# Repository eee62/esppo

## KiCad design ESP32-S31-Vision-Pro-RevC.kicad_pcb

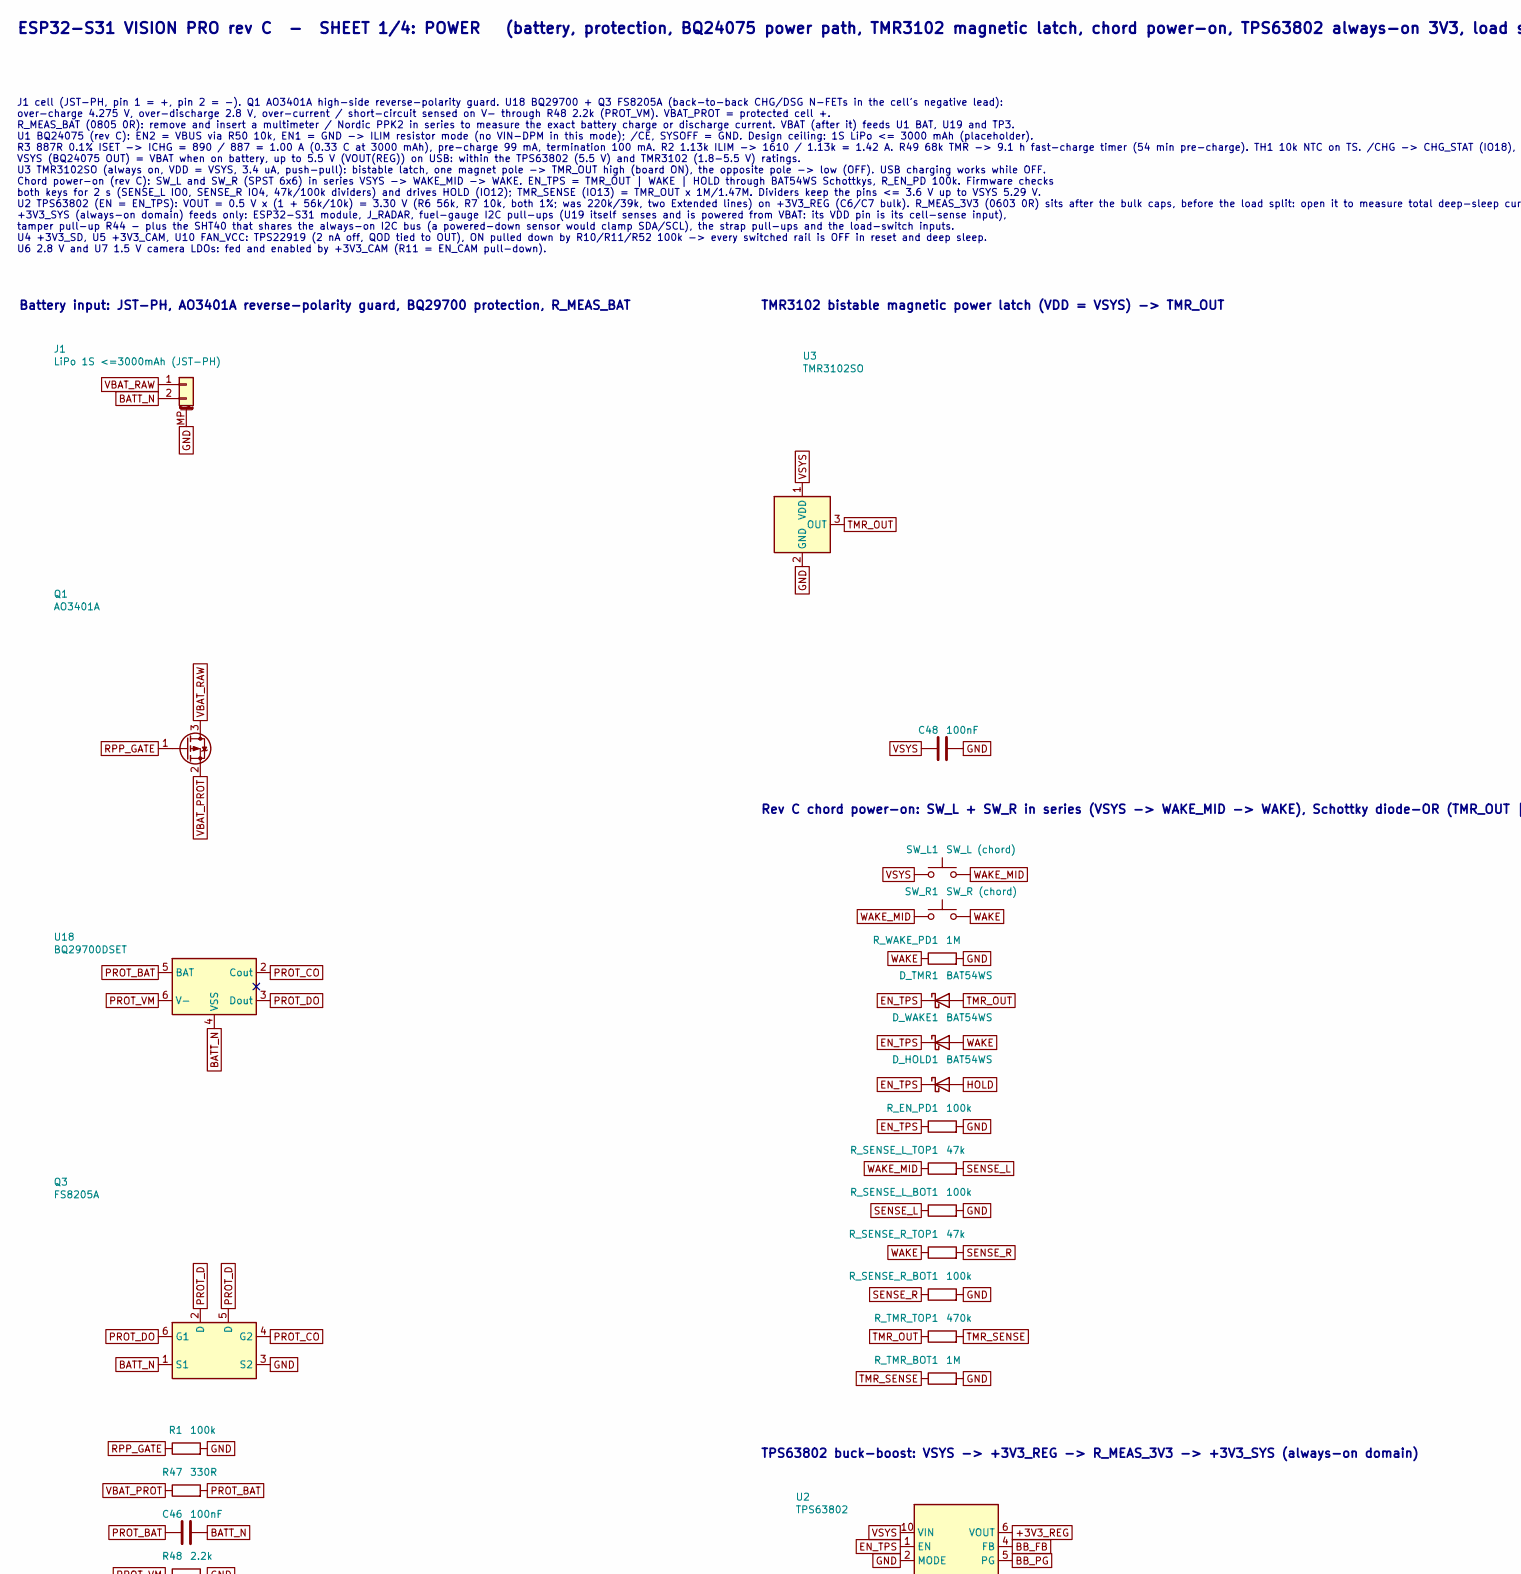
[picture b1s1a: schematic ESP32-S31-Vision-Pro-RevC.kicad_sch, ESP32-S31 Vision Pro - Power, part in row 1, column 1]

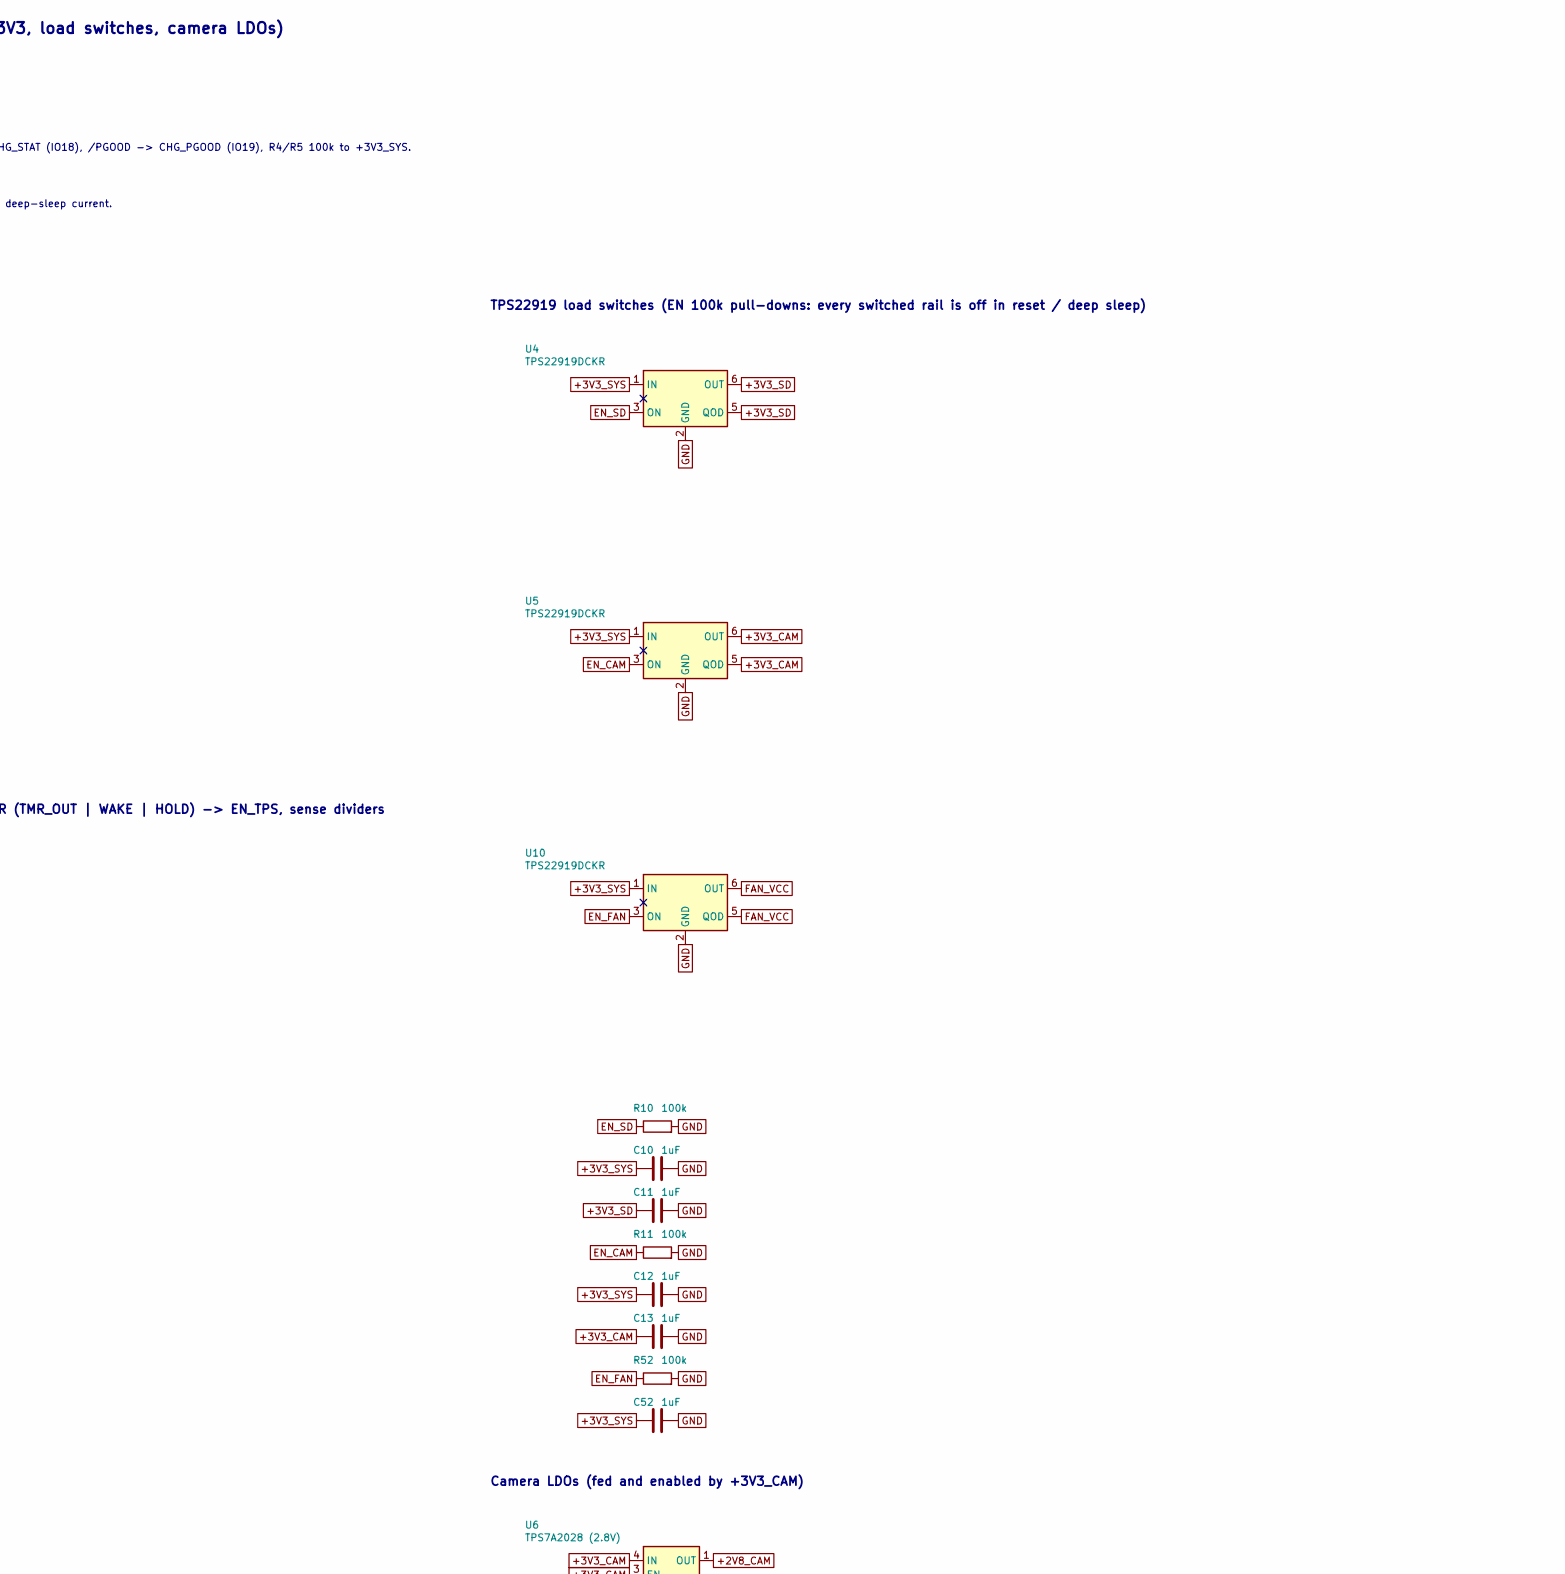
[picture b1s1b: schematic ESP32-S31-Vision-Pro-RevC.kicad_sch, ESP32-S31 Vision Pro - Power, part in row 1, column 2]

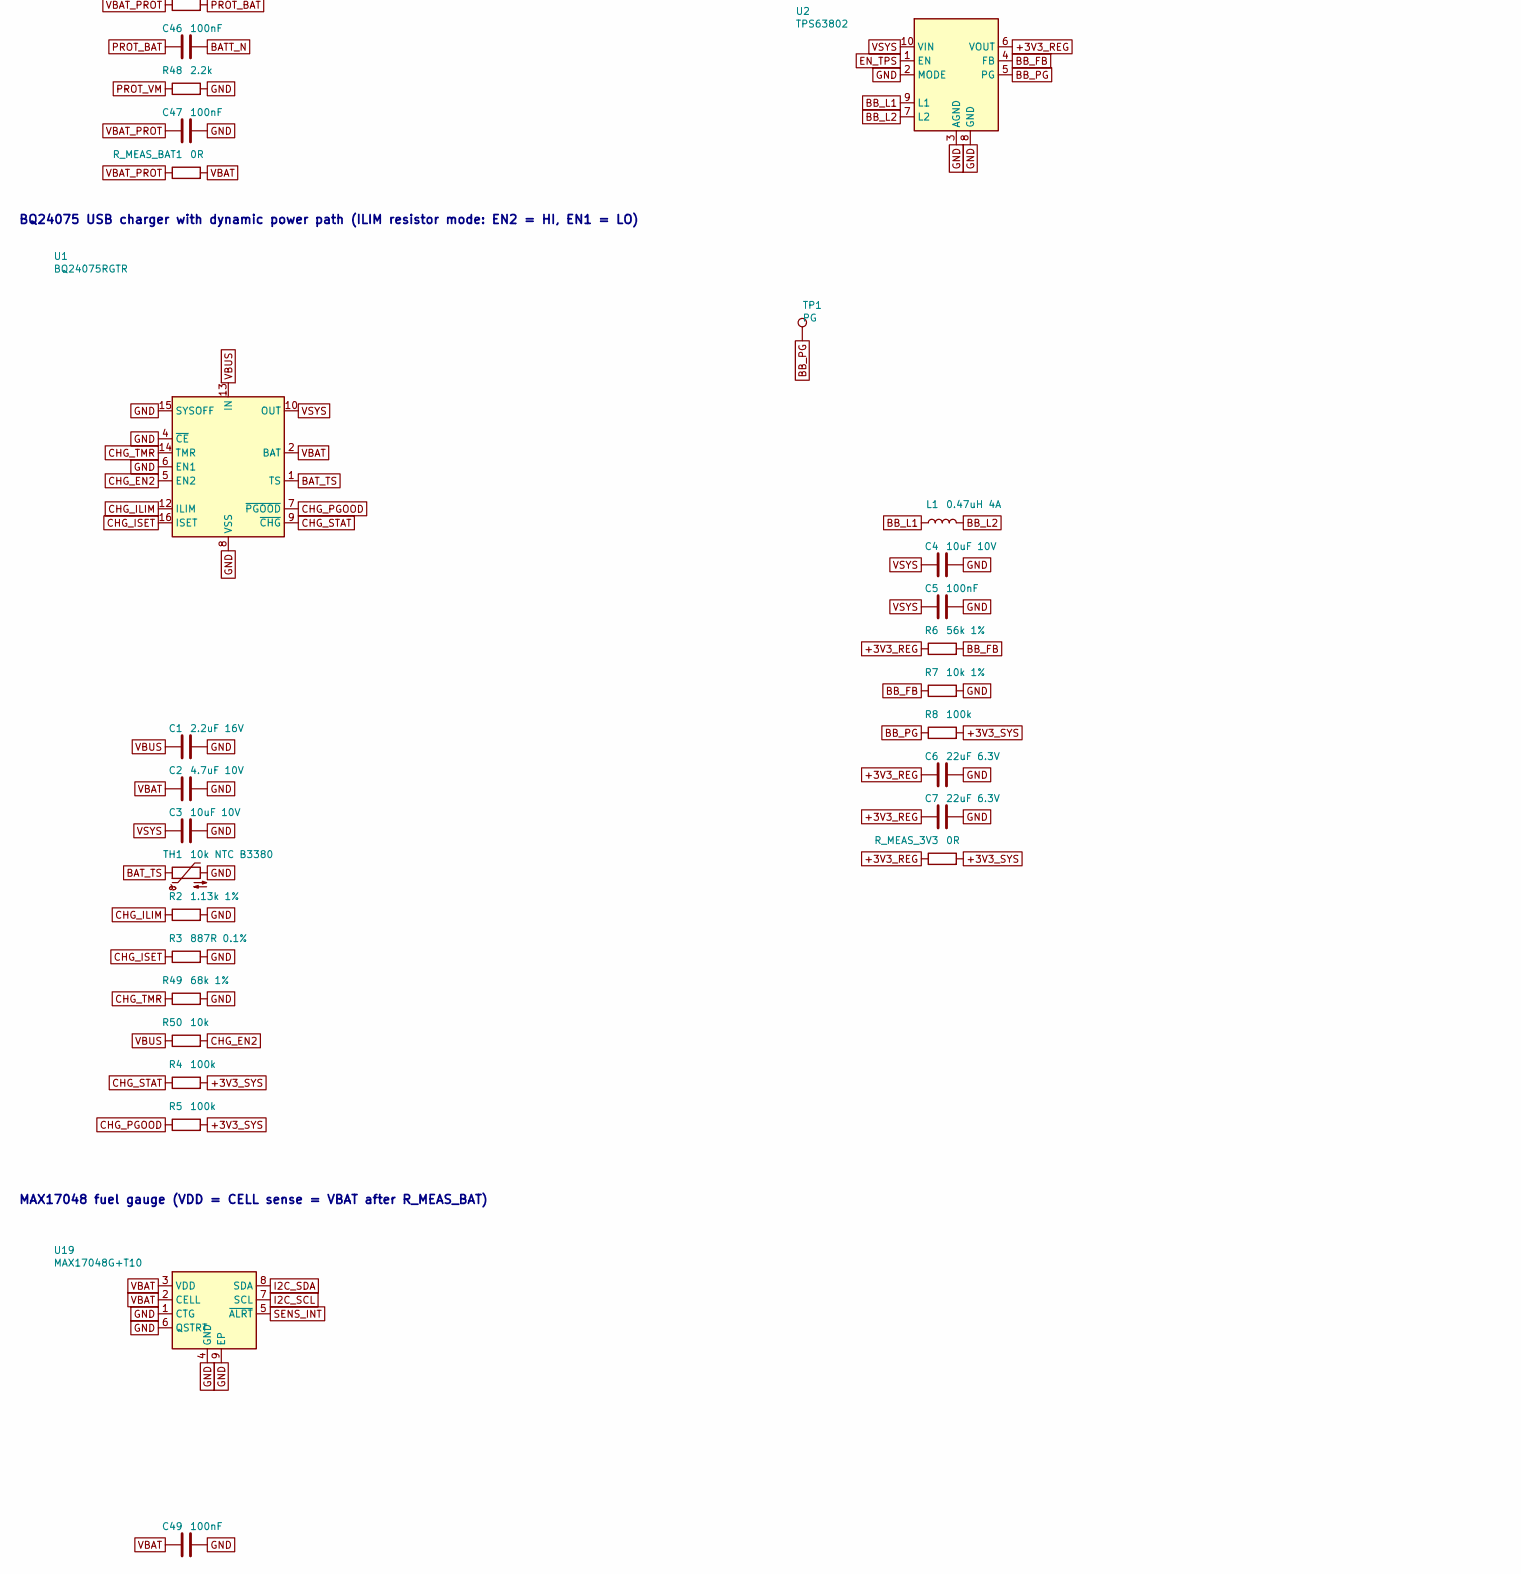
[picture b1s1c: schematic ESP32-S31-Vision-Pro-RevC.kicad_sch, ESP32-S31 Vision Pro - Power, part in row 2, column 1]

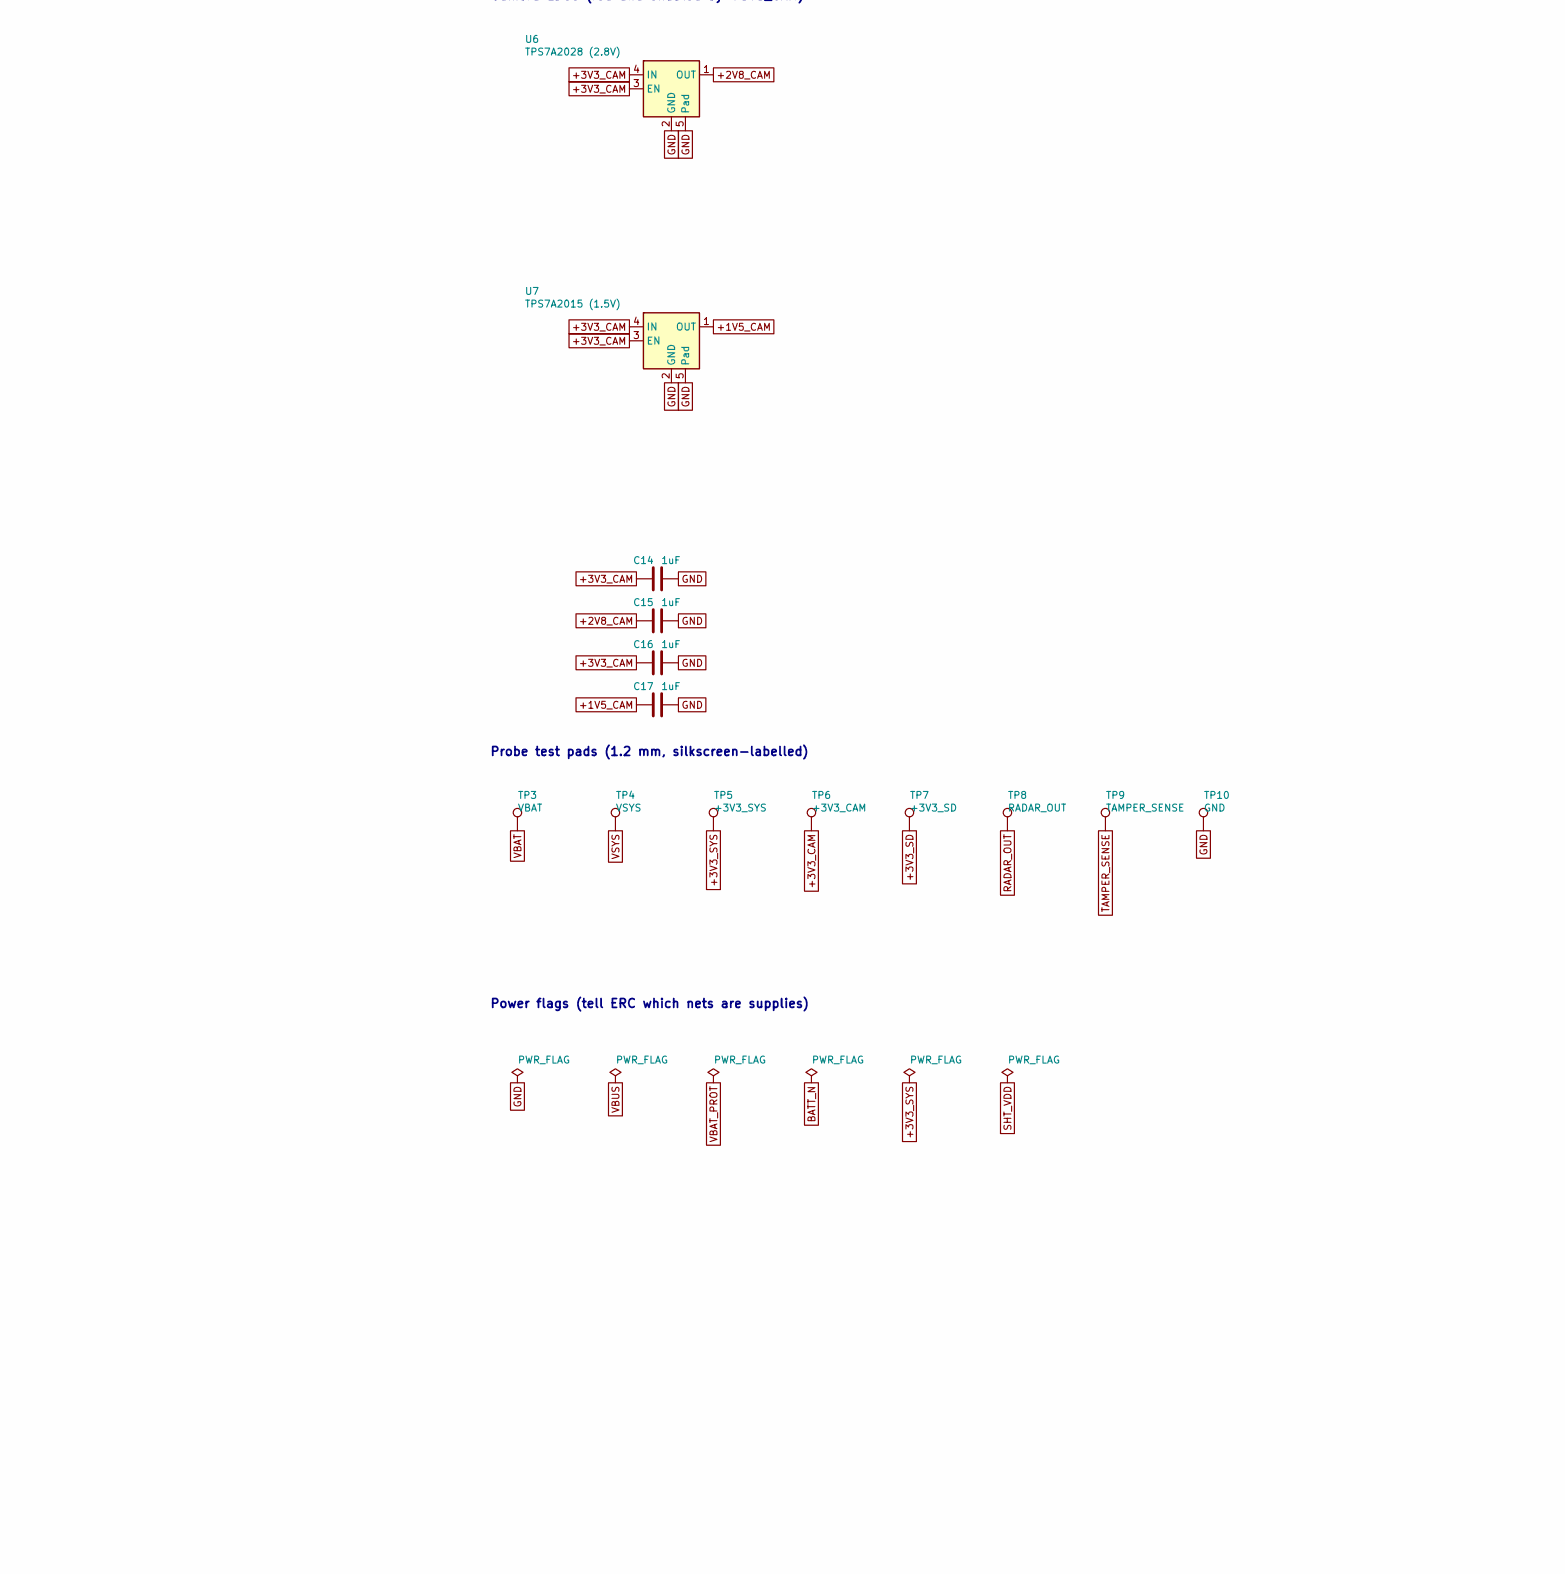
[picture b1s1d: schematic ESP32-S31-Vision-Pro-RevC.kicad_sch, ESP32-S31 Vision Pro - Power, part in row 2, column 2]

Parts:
C1: 2.2uF 16V; C_0603_1608Metric; MPN CL10A225KO8NNNC; LCSC C23630
C2: 4.7uF 10V; C_0603_1608Metric; MPN CL10A475KO8NNNC; LCSC C19666
C3, C4: 10uF 10V; C_0603_1608Metric; MPN CL10A106KP8NNNC; LCSC C19702
C5, C46, C47, C48, C49: 100nF; C_0402_1005Metric; MPN CL05B104KO5NNNC; LCSC C1525
C6, C7: 22uF 6.3V; C_0603_1608Metric; MPN CL10A226MQ8NRNC; LCSC C59461
C10, C11, C12, C13, C14, C15, C16, C17, C52: 1uF; C_0402_1005Metric; MPN CL05A105KA5NQNC; LCSC C52923
D_HOLD1: BAT54WS; D_SOD-323; MPN BAT54WS; LCSC C7502694
D_TMR1: BAT54WS; D_SOD-323; MPN BAT54WS; LCSC C7502694
D_WAKE1: BAT54WS; D_SOD-323; MPN BAT54WS; LCSC C7502694
J1: LiPo 1S <=3000mAh (JST-PH); JST_PH_S2B-PH-SM4-TB_1x02-1MP_P2.00mm_Horizontal; MPN S2B-PH-SM4-TB(LF)(SN); LCSC C295747
L1: 0.47uH 4A; L_1008_2520Metric; MPN DFE252012F-R47M=P2; LCSC C703140
Q1: AO3401A; SOT-23; MPN AO3401A; LCSC C15127
Q3: FS8205A; SOT-23-6; MPN FS8205A; LCSC C908265
R1, R4, R5, R8, R10, R11, R52: 100k; R_0402_1005Metric; MPN 0402WGF1003TCE; LCSC C25741
R2: 1.13k 1%; R_0402_1005Metric; MPN 0402WGF1131TCE; LCSC C67014
R3: 887R 0.1%; R_0402_1005Metric; MPN RT0402BRD07887RL; LCSC C852938
R6: 56k 1%; R_0402_1005Metric; MPN 0402WGF5602TCE; LCSC C25796
R7: 10k 1%; R_0402_1005Metric; MPN 0402WGF1002TCE; LCSC C25744
R47: 330R; R_0402_1005Metric; MPN 0402WGF3300TCE; LCSC C25104
R48: 2.2k; R_0402_1005Metric; MPN 0402WGF2201TCE; LCSC C25879
R49: 68k 1%; R_0402_1005Metric; MPN 0402WGF6802TCE; LCSC C36871
R50: 10k; R_0402_1005Metric; MPN 0402WGF1002TCE; LCSC C25744
R_EN_PD1: 100k; R_0402_1005Metric; MPN 0402WGF1003TCE; LCSC C25741
R_MEAS_3V3: 0R; R_0603_1608Metric; MPN 0603WAF0000T5E; LCSC C21189
R_MEAS_BAT1: 0R; R_0805_2012Metric; MPN 0805W8F0000T5E; LCSC C17477
R_SENSE_L_BOT1: 100k; R_0402_1005Metric; MPN 0402WGF1003TCE; LCSC C25741
R_SENSE_L_TOP1: 47k; R_0402_1005Metric; MPN 0402WGF4702TCE; LCSC C25792
R_SENSE_R_BOT1: 100k; R_0402_1005Metric; MPN 0402WGF1003TCE; LCSC C25741
R_SENSE_R_TOP1: 47k; R_0402_1005Metric; MPN 0402WGF4702TCE; LCSC C25792
R_TMR_BOT1: 1M; R_0402_1005Metric; MPN 0402WGF1004TCE; LCSC C26083
R_TMR_TOP1: 470k; R_0402_1005Metric; MPN 0402WGF4703TCE; LCSC C25790
R_WAKE_PD1: 1M; R_0402_1005Metric; MPN 0402WGF1004TCE; LCSC C26083
SW_L1: SW_L (chord); SW_SPST_PTS645Sx43SMTR92; MPN PTS645SK43SMTR92LFS; LCSC C221871
SW_R1: SW_R (chord); SW_SPST_PTS645Sx43SMTR92; MPN PTS645SK43SMTR92LFS; LCSC C221871
TH1: 10k NTC B3380; R_0402_1005Metric; MPN NCP15XH103F03RC; LCSC C77131
TP1: PG; TestPoint_Pad_D1.0mm
TP3: VBAT; TestPoint_Pad_D1.2mm
TP4: VSYS; TestPoint_Pad_D1.2mm
TP5: +3V3_SYS; TestPoint_Pad_D1.2mm
TP6: +3V3_CAM; TestPoint_Pad_D1.2mm
TP7: +3V3_SD; TestPoint_Pad_D1.2mm
TP8: RADAR_OUT; TestPoint_Pad_D1.2mm
TP9: TAMPER_SENSE; TestPoint_Pad_D1.2mm
TP10: GND; TestPoint_Pad_D1.2mm
U1: BQ24075RGTR; VQFN-16-1EP_3x3mm_P0.5mm_EP1.6x1.6mm; MPN BQ24075RGTR; LCSC C15464
U2: TPS63802; Texas_DLA0010A_VSON-HR-10_2x3mm_P0.5mm; MPN TPS63802DLAT; LCSC C1849531
U3: TMR3102SO; SOT-23; MPN TMR3102SO; LCSC C7421000
U4, U5, U10: TPS22919DCKR; SOT-363_SC-70-6; MPN TPS22919DCKR; LCSC C2149796
U6: TPS7A2028 (2.8V); Texas_X2SON-4_1x1mm_P0.65mm; MPN TPS7A2028PDQNR-A-TP; LCSC C55191366
U7: TPS7A2015 (1.5V); Texas_X2SON-4_1x1mm_P0.65mm; MPN TPS7A2015PDQNR; LCSC C2862700
U18: BQ29700DSET; WSON-6_1.5x1.5mm_P0.5mm; MPN BQ29700DSET; LCSC C2876282
U19: MAX17048G+T10; TDFN-8-1EP_2x2mm_P0.5mm_EP0.8x1.2mm; MPN MAX17048G+T10; LCSC C2682616

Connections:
+1V5_CAM: C17.1, U7.1 (OUT); also elsewhere on the board
+2V8_CAM: C15.1, U6.1 (OUT); also elsewhere on the board
+3V3_CAM: C13.1, C14.1, C16.1, TP6.1, U5.5 (QOD), U5.6 (OUT), U6.3 (EN), U6.4 (IN), U7.3 (EN), U7.4 (IN)
+3V3_REG: C6.1, C7.1, R6.1, R_MEAS_3V3.1, U2.6 (VOUT)
+3V3_SD: C11.1, TP7.1, U4.5 (QOD), U4.6 (OUT); also elsewhere on the board
+3V3_SYS: C10.1, C12.1, C52.1, R4.2, R5.2, R8.2, R_MEAS_3V3.2, TP5.1, U4.1 (IN), U5.1 (IN), U10.1 (IN); also elsewhere on the board
BATT_N: C46.2, J1.2, Q3.1 (S1), U18.4 (VSS)
BAT_TS: TH1.1, U1.1 (TS)
BB_FB: R6.2, R7.1, U2.4 (FB)
BB_L1: L1.1, U2.9 (L1)
BB_L2: L1.2, U2.7 (L2)
BB_PG: R8.1, TP1.1, U2.5 (PG)
CHG_EN2: R50.2, U1.5 (EN2)
CHG_ILIM: R2.1, U1.12 (ILIM)
CHG_ISET: R3.1, U1.16 (ISET)
CHG_PGOOD: R5.1, U1.7 (~PGOOD); also elsewhere on the board
CHG_STAT: R4.1, U1.9 (~CHG); also elsewhere on the board
CHG_TMR: R49.1, U1.14 (TMR)
EN_CAM: R11.1, U5.3 (ON); also elsewhere on the board
EN_FAN: R52.1, U10.3 (ON); also elsewhere on the board
EN_SD: R10.1, U4.3 (ON); also elsewhere on the board
EN_TPS: D_HOLD1.1 (K), D_TMR1.1 (K), D_WAKE1.1 (K), R_EN_PD1.1, U2.1 (EN)
FAN_VCC: U10.5 (QOD), U10.6 (OUT); also elsewhere on the board
GND: C1.2, C2.2, C3.2, C4.2, C5.2, C6.2, C7.2, C10.2, C11.2, C12.2, C13.2, C14.2, C15.2, C16.2, C17.2, C47.2, C48.2, C49.2, C52.2, J1.MP (MountPin), Q3.3 (S2), R1.2, R2.2, R3.2, R7.2, R10.2, R11.2, R48.2, R49.2, R52.2, R_EN_PD1.2, R_SENSE_L_BOT1.2, R_SENSE_R_BOT1.2, R_TMR_BOT1.2, R_WAKE_PD1.2, TH1.2, TP10.1, U1.4 (~CE), U1.6 (EN1), U1.8 (VSS), U1.15 (SYSOFF), U1.17 (VSS), U2.2 (MODE), U2.3 (AGND), U2.8 (GND), U3.2 (GND), U4.2 (GND), U5.2 (GND), U6.2 (GND), U6.5 (Pad), U7.2 (GND), U7.5 (Pad), U10.2 (GND), U19.1 (CTG), U19.4 (GND), U19.6 (QSTRT), U19.9 (EP); also elsewhere on the board
HOLD: D_HOLD1.2 (A); also elsewhere on the board
I2C_SCL: U19.7 (SCL); also elsewhere on the board
I2C_SDA: U19.8 (SDA); also elsewhere on the board
PROT_BAT: C46.1, R47.2, U18.5 (BAT)
PROT_CO: Q3.4 (G2), U18.2 (Cout)
PROT_D: Q3.2 (D), Q3.5 (D)
PROT_DO: Q3.6 (G1), U18.3 (Dout)
PROT_VM: R48.1, U18.6 (V-)
RADAR_OUT: TP8.1; also elsewhere on the board
RPP_GATE: Q1.1 (G), R1.1
SENSE_L: R_SENSE_L_BOT1.1, R_SENSE_L_TOP1.2; also elsewhere on the board
SENSE_R: R_SENSE_R_BOT1.1, R_SENSE_R_TOP1.2; also elsewhere on the board
SENS_INT: U19.5 (~ALRT); also elsewhere on the board
TAMPER_SENSE: TP9.1; also elsewhere on the board
TMR_OUT: D_TMR1.2 (A), R_TMR_TOP1.1, U3.3 (OUT)
TMR_SENSE: R_TMR_BOT1.1, R_TMR_TOP1.2; also elsewhere on the board
VBAT: C2.1, C49.1, R_MEAS_BAT1.2, TP3.1, U1.2 (BAT), U1.3 (BAT), U19.2 (CELL), U19.3 (VDD)
VBAT_PROT: C47.1, Q1.2 (S), R47.1, R_MEAS_BAT1.1
VBAT_RAW: J1.1, Q1.3 (D)
VBUS: C1.1, R50.1, U1.13 (IN); also elsewhere on the board
VSYS: C3.1, C4.1, C5.1, C48.1, SW_L1.1, TP4.1, U1.10 (OUT), U1.11 (OUT), U2.10 (VIN), U3.1 (VDD)
WAKE: D_WAKE1.2 (A), R_SENSE_R_TOP1.1, R_WAKE_PD1.1, SW_R1.2
WAKE_MID: R_SENSE_L_TOP1.1, SW_L1.2, SW_R1.1

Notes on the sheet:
ESP32-S31 VISION PRO rev C - SHEET 1/4: POWER (battery, protection, BQ24075 power path, TMR3102 magnetic latch, chord power-on, TPS63802 always-on 3V3, load switches, camera LDOs)
J1 cell (JST-PH, pin 1 = +, pin 2 = -). Q1 AO3401A high-side reverse-polarity guard. U18 BQ29700 + Q3 FS8205A (back-to-back CHG/DSG N-FETs in the cell's negative lead): over-charge 4.275 V, over-discharge 2.8 V, over-current / short-circuit sensed on V- through R48 2.2k (PROT_VM). VBAT_PROT = prote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
Battery input: JST-PH, AO3401A reverse-polarity guard, BQ29700 protection, R_MEAS_BAT
BQ24075 USB charger with dynamic power path (ILIM resistor mode: EN2 = HI, EN1 = LO)
MAX17048 fuel gauge (VDD = CELL sense = VBAT after R_MEAS_BAT)
TMR3102 bistable magnetic power latch (VDD = VSYS) -> TMR_OUT
Rev C chord power-on: SW_L + SW_R in series (VSYS -> WAKE_MID -> WAKE), Schottky diode-OR (TMR_OUT | WAKE | HOLD) -> EN_TPS, sense dividers
TPS63802 buck-boost: VSYS -> +3V3_REG -> R_MEAS_3V3 -> +3V3_SYS (always-on domain)
TPS22919 load switches (EN 100k pull-downs: every switched rail is off in reset / deep sleep)
Camera LDOs (fed and enabled by +3V3_CAM)
Probe test pads (1.2 mm, silkscreen-labelled)
Power flags (tell ERC which nets are supplies)
Sub-sheets

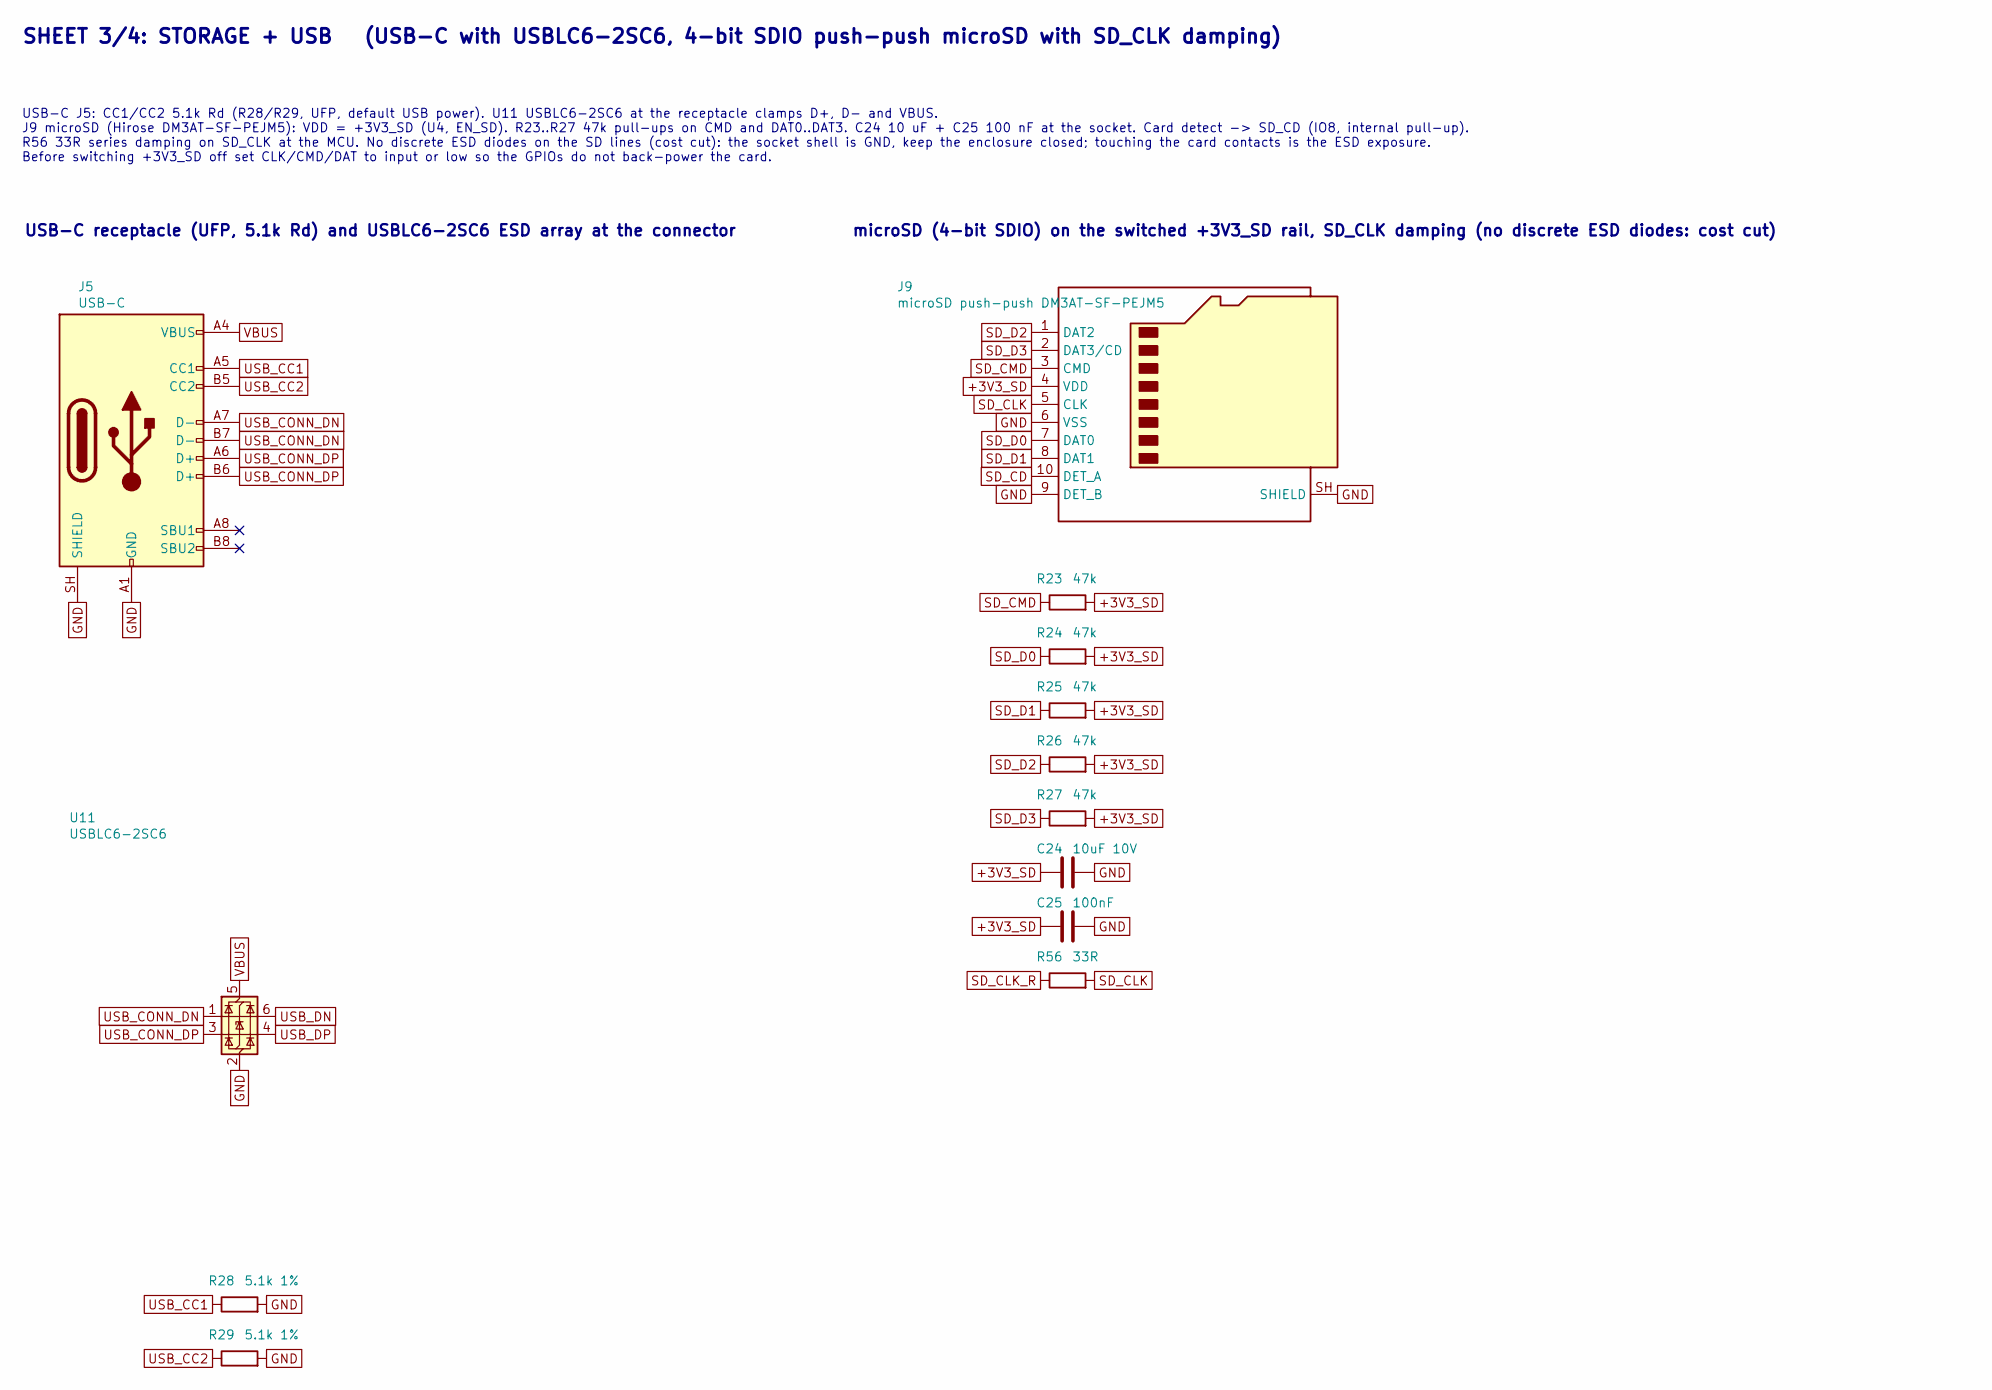
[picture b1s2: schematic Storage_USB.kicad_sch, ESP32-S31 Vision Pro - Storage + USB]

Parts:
C24: 10uF 10V; C_0603_1608Metric; MPN CL10A106KP8NNNC; LCSC C19702
C25: 100nF; C_0402_1005Metric; MPN CL05B104KO5NNNC; LCSC C1525
J5: USB-C; USB_C_Receptacle_GCT_USB4110; MPN USB4110-GF-A; LCSC C5143397
J9: microSD push-push DM3AT-SF-PEJM5; microSD_HC_Hirose_DM3AT-SF-PEJM5; MPN DM3AT-SF-PEJM5; LCSC C114218
R23, R24, R25, R26, R27: 47k; R_0402_1005Metric; MPN 0402WGF4702TCE; LCSC C25792
R28, R29: 5.1k 1%; R_0402_1005Metric; MPN 0402WGF5101TCE; LCSC C25905
R56: 33R; R_0402_1005Metric; MPN 0402WGF330JTCE; LCSC C25105
U11: USBLC6-2SC6; SOT-23-6; MPN USBLC6-2SC6; LCSC C7519

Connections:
+3V3_SD: C24.1, C25.1, J9.4 (VDD), R23.2, R24.2, R25.2, R26.2, R27.2; also elsewhere on the board
GND: C24.2, C25.2, J5.A1 (GND), J5.A12 (GND), J5.B1 (GND), J5.B12 (GND), J5.SH (SHIELD), J9.6 (VSS), J9.9 (DET_B), J9.SH (SHIELD), R28.2, R29.2, U11.2 (GND); also elsewhere on the board
SD_CD: J9.10 (DET_A); also elsewhere on the board
SD_CLK: J9.5 (CLK), R56.2
SD_CLK_R: R56.1; also elsewhere on the board
SD_CMD: J9.3 (CMD), R23.1; also elsewhere on the board
SD_D0: J9.7 (DAT0), R24.1; also elsewhere on the board
SD_D1: J9.8 (DAT1), R25.1; also elsewhere on the board
SD_D2: J9.1 (DAT2), R26.1; also elsewhere on the board
SD_D3: J9.2 (DAT3/CD), R27.1; also elsewhere on the board
USB_CC1: J5.A5 (CC1), R28.1
USB_CC2: J5.B5 (CC2), R29.1
USB_CONN_DN: J5.A7 (D-), J5.B7 (D-), U11.1 (I/O1)
USB_CONN_DP: J5.A6 (D+), J5.B6 (D+), U11.3 (I/O2)
USB_DN: U11.6 (I/O1); also elsewhere on the board
USB_DP: U11.4 (I/O2); also elsewhere on the board
VBUS: J5.A4 (VBUS), J5.A9 (VBUS), J5.B4 (VBUS), J5.B9 (VBUS), U11.5 (VBUS); also elsewhere on the board

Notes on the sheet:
SHEET 3/4: STORAGE + USB (USB-C with USBLC6-2SC6, 4-bit SDIO push-push microSD with SD_CLK damping)
USB-C J5: CC1/CC2 5.1k Rd (R28/R29, UFP, default USB power). U11 USBLC6-2SC6 at the receptacle clamps D+, D- and VBUS. J9 microSD (Hirose DM3AT-SF-PEJM5): VDD = +3V3_SD (U4, EN_SD). R23..R27 47k pull-ups on CMD and DAT0..DAT3. C24 10 uF + C25 100 nF at the socket. Card detect -> SD_CD (IO8, interna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
USB-C receptacle (UFP, 5.1k Rd) and USBLC6-2SC6 ESD array at the connector
microSD (4-bit SDIO) on the switched +3V3_SD rail, SD_CLK damping (no discrete ESD diodes: cost cut)
